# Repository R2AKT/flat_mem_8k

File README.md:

License addendum - https://github.com/R2AKT/flat_mem_8k/blob/main/Addendum.txt
# flat_mem_8k

8k flat (linear) memory board: 2k ROM + 2k EEPROM/RAM + 2k EEPROM/RAM + 2k RAM.
For Mega-80 (Mega-580) DIY 8-bit micro-computer - https://github.com/R2AKT/Mega-80.

ROM - 2k;
PROM - 4/2k;
RAM - 2/4k.

Status: tested in conjunction with the processor module at a frequency of up to 3 MHz (quartz resonator 27 MHz).

Плата плоской (линейной) памяти на 8к.
Для самодельной 8-битной микро-ЭВМ - https://github.com/R2AKT/Mega-80.

ПЗУ - 2кб;
ППЗУ - 4/2кб;
ОЗУ - 2/4кб.

Статус: проверено совместно с процессорным модулем на частоте до 3 МГц (кварцевый резонатор 27 МГц).

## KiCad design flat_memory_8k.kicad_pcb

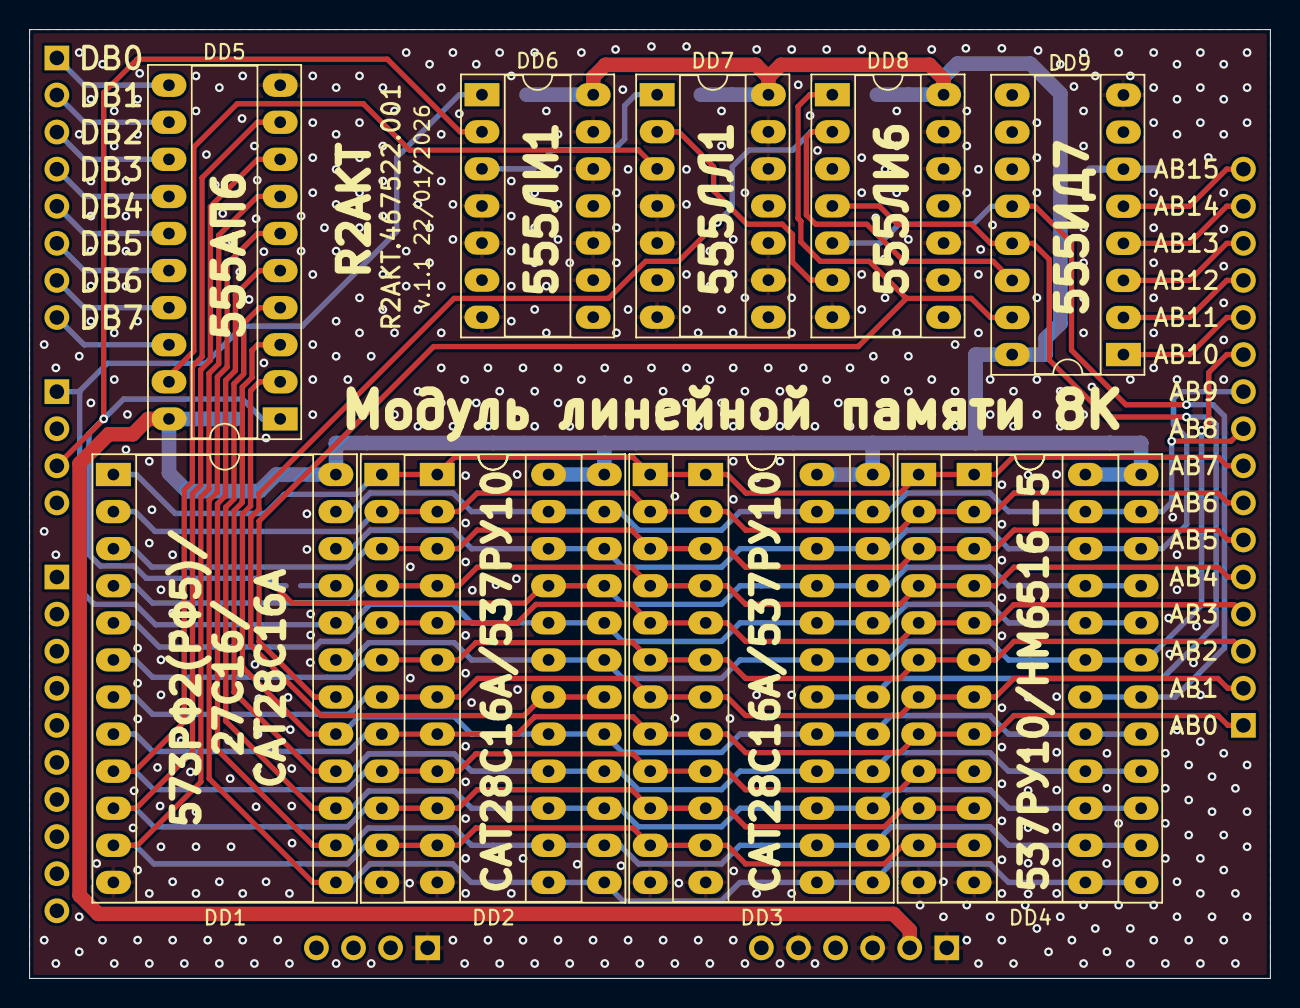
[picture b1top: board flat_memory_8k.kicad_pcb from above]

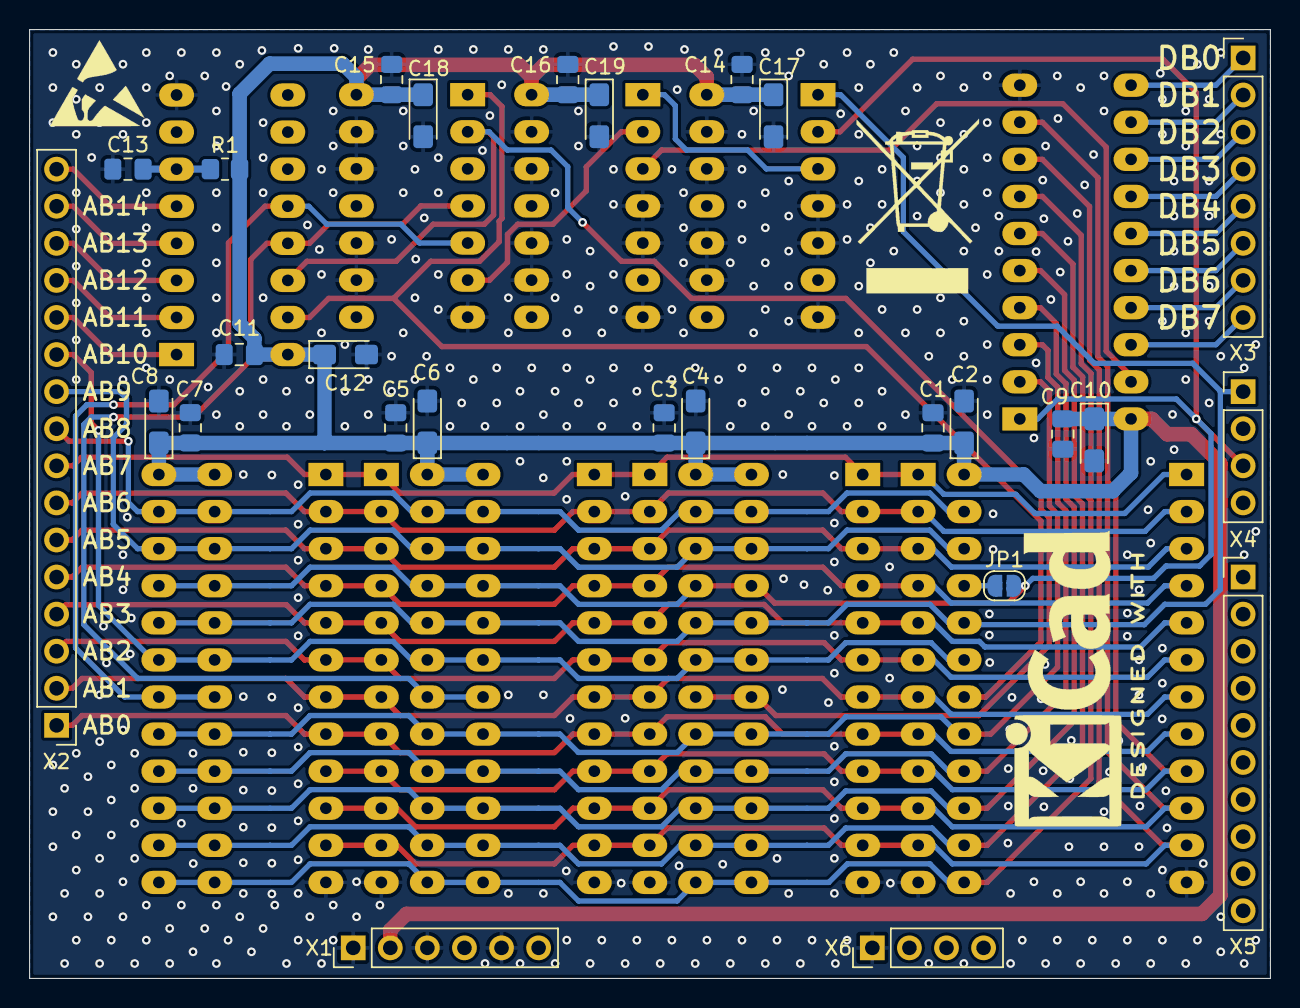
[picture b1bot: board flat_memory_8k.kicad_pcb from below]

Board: 2 copper layers, 85.0 x 65.0 mm, 39 parts (27 on the bottom side), 45 nets.

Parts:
C1, C3, C5, C7, C9, C11, C13, C14, C15, C16: 100n; C_0805_2012Metric_Pad1.18x1.45mm_HandSolder
C2, C4, C6, C8, C10, C12, C17, C18, C19: 1u; CP_EIA-3216-18_Kemet-A_Pad1.58x1.35mm_HandSolder
DD1: 573РФ2 (2716); DIP-24_W15.24mm_Socket_LongPads
DD2: CAT28C16A; DIP-24_W15.24mm_Socket_LongPads
DD3, DD4: 537РУ10; DIP-24_W15.24mm_Socket_LongPads
DD5: 555АП6 (74LS245); DIP-20_W7.62mm_Socket_LongPads
DD6: 555ЛИ1 (74LS08); DIP-14_W7.62mm_Socket_LongPads
DD7: 555ЛЛ1 (74LS32); DIP-14_W7.62mm_Socket_LongPads
DD8: 555ЛИ6 (74LS21); DIP-14_W7.62mm_Socket_LongPads
DD9: 555ИД7 (74LS138); DIP-16_W7.62mm_Socket_LongPads
DD10, DD11, DD12: DUAL SOCKET; DIP-24_W7.62mm_LongPads
JP1: Jumper_2_Open; SolderJumper-2_P1.3mm_Open_RoundedPad1.0x1.5mm
R1: 1k; R_0805_2012Metric_Pad1.20x1.40mm_HandSolder
X1: Power; PinHeader_1x06_P2.54mm_Vertical
X2: Address; PinHeader_1x16_P2.54mm_Vertical
X3: Data; PinHeader_1x08_P2.54mm_Vertical
X4: Mode; PinHeader_1x04_P2.54mm_Vertical
X5: Control; PinHeader_1x10_P2.54mm_Vertical
X6: Clock; PinHeader_1x04_P2.54mm_Vertical

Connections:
+5: C1.1, C2.1, C3.1, C4.1, C5.1, C6.1, C7.1, C8.1, C9.1, C10.1, C11.1, C12.1, C14.1, C15.1, C16.1, C17.1, C18.1, C19.1, DD1.24 (VCC), DD2.24 (VCC), DD3.24 (VCC), DD4.24 (VCC), DD5.20 (VCC), DD6.14 (VCC), DD7.14 (VCC), DD8.14 (VCC), DD9.16 (VCC), DD10.24 (VCC), DD11.24 (VCC), DD12.24 (VCC), R1.2, X1.2
/AB0: DD1.8 (A0), DD2.8 (A0), DD3.8 (A10), DD4.8 (A10), DD10.8 (A0), DD11.8 (A10), DD12.8 (A10), X2.1
/AB1: DD1.7 (A1), DD2.7 (A1), DD3.7 (A9), DD4.7 (A9), DD10.7 (A1), DD11.7 (A9), DD12.7 (A9), X2.2
/AB2: DD1.6 (A2), DD2.6 (A2), DD3.6 (A8), DD4.6 (A8), DD10.6 (A2), DD11.6 (A8), DD12.6 (A8), X2.3
/AB3: DD1.5 (A3), DD2.5 (A3), DD3.5 (A7), DD4.5 (A7), DD10.5 (A3), DD11.5 (A7), DD12.5 (A7), X2.4
/AB4: DD1.4 (A4), DD2.4 (A4), DD3.4 (A6), DD4.4 (A6), DD10.4 (A4), DD11.4 (A6), DD12.4 (A6), X2.5
/AB5: DD1.3 (A5), DD2.3 (A5), DD3.3 (A5), DD4.3 (A5), DD10.3 (A5), DD11.3 (A5), DD12.3 (A5), X2.6
/AB6: DD1.2 (A6), DD2.2 (A6), DD3.2 (A4), DD4.2 (A4), DD10.2 (A6), DD11.2 (A4), DD12.2 (A4), X2.7
/AB7: DD1.1 (A7), DD2.1 (A7), DD3.1 (A3), DD4.1 (A3), DD10.1 (A7), DD11.1 (A3), DD12.1 (A3), X2.8
/AB8: DD1.23 (A8), DD2.23 (A8), DD3.23 (A2), DD4.23 (A2), DD10.23 (A8), DD11.23 (A2), DD12.23 (A2), X2.9
/AB9: DD1.22 (A9), DD2.22 (A9), DD3.22 (A1), DD4.22 (A1), DD10.22 (A9), DD11.22 (A1), DD12.22 (A1), X2.10
/AB10: DD1.19 (A10), DD2.19 (A10), DD3.19 (A0), DD4.19 (A0), DD10.19 (A10), DD11.19 (A0), DD12.19 (A0), X2.11
/AB11: DD9.1 (A0), X2.12
/AB12: DD9.2 (A1), X2.13
/AB13: DD9.3 (A2), X2.14
/AB14: DD9.4 (E1), X2.15
/AB15: DD9.5 (E2), X2.16
/DATA_B0: DD1.9 (Q0), DD2.9 (Q0), DD3.9 (Q0), DD4.9 (Q0), DD5.9 (A7), DD10.9 (Q0), DD11.9 (Q0), DD12.9 (Q0)
/DATA_B1: DD1.10 (Q1), DD2.10 (Q1), DD3.10 (Q1), DD4.10 (Q1), DD5.8 (A6), DD10.10 (Q1), DD11.10 (Q1), DD12.10 (Q1)
/DATA_B2: DD1.11 (Q2), DD2.11 (Q2), DD3.11 (Q2), DD4.11 (Q2), DD5.7 (A5), DD10.11 (Q2), DD11.11 (Q2), DD12.11 (Q2)
/DATA_B3: DD1.13 (Q3), DD2.13 (Q3), DD3.13 (Q3), DD4.13 (Q3), DD5.6 (A4), DD10.13 (Q3), DD11.13 (Q3), DD12.13 (Q3)
/DATA_B4: DD1.14 (Q4), DD2.14 (Q4), DD3.14 (Q4), DD4.14 (Q4), DD5.5 (A3), DD10.14 (Q4), DD11.14 (Q4), DD12.14 (Q4)
/DATA_B5: DD1.15 (Q5), DD2.15 (Q5), DD3.15 (Q5), DD4.15 (Q5), DD5.4 (A2), DD10.15 (Q5), DD11.15 (Q5), DD12.15 (Q5)
/DATA_B6: DD1.16 (Q6), DD2.16 (Q6), DD3.16 (Q6), DD4.16 (Q6), DD5.3 (A1), DD10.16 (Q6), DD11.16 (Q6), DD12.16 (Q6)
/DATA_B7: DD1.17 (Q7), DD2.17 (Q7), DD3.17 (Q7), DD4.17 (Q7), DD5.2 (A0), DD10.17 (Q7), DD11.17 (Q7), DD12.17 (Q7)
/DB0: DD5.11 (B7), X3.1
/DB1: DD5.12 (B6), X3.2
/DB2: DD5.13 (B5), X3.3
/DB3: DD5.14 (B4), X3.4
/DB4: DD5.15 (B3), X3.5
/DB5: DD5.16 (B2), X3.6
/DB6: DD5.17 (B1), X3.7
/DB7: DD5.18 (B0), X3.8
/~2K_CS: DD1.18 (~CE), DD8.1, DD9.15 (O0)
/~4K_CS: DD2.18 (~CE), DD8.2, DD9.14 (O1), DD10.18 (~CE)
/~6K_CS: DD3.18 (~CE), DD8.4, DD9.13 (O2), DD11.18 (~CE)
/~8K_CS: DD4.18 (~CE), DD8.5, DD9.12 (O3), DD12.18 (~CE)
/~MEMR: DD1.20 (~OE), DD2.20 (~OE), DD3.20 (~OE), DD4.20 (~OE), DD6.1, DD10.20 (~OE), DD11.20 (~OE), DD12.20 (~OE), X4.1
/~MEMW: DD2.21 (~WE), DD3.21 (~WE), DD4.21 (~WE), DD5.1 (A->B), DD6.2, DD10.21 (~WE), DD11.21 (~WE), DD12.21 (~WE), JP1.2 (B), X4.3
GND: C1.2, C2.2, C3.2, C4.2, C5.2, C6.2, C7.2, C8.2, C9.2, C10.2, C11.2, C12.2, C13.1, C14.2, C15.2, C16.2, C17.2, C18.2, C19.2, DD1.12 (GND), DD2.12 (GND), DD3.12 (GND), DD4.12 (GND), DD5.10 (GND), DD6.4, DD6.5, DD6.7 (GND), DD6.9, DD6.10, DD6.12, DD6.13, DD7.4, DD7.5, DD7.7 (GND), DD7.9, DD7.10, DD7.12, DD7.13, DD8.7 (GND), DD8.9, DD8.10, DD8.12, DD8.13, DD9.8 (GND), DD10.12 (GND), DD11.12 (GND), DD12.12 (GND), X1.1, X1.3, X1.5, X6.1
unnamed: DD1.21 (Vpp), JP1.1 (A)
unnamed: DD5.19 (CE), DD7.3
unnamed: DD6.3, DD7.1
unnamed: DD7.2, DD8.6
unnamed: C13.2, DD9.6 (E3), R1.1

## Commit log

2026-01-27 Add files via upload
    Add optional footprint for memory
    Добавлены опциональные посадочные места памяти
2026-06-17 Fix silk

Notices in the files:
README.md:
License: MIT
